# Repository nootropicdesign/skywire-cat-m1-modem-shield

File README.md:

# Skywire Shield: Arduino shield for Nimbelink Skywire CAT M1 and NB-IoT modems

This is a design for a simple Arduino shield for Nimbelink Skywire CAT M1 and NB-IoT modems. Nimbelink modems are designed to have compatible pinouts and electrical characteristics, so it is possible to design a carrier board that works for a large variety of modems. The board has a switching power supply that provides 3.8V to the modem. Jumpers can be used to connect the modem's serial RX and TX to the Arduino hardware serial pins or to pins for use with software serial (digital pins 2 and 3).

A standard 6-pin serial header connection is accessible from the bottom of the board. This is because some modem modules come with a very high default serial rate that must be changed before an Arduino can interface with it. For example, the Sequans Monarch modem has a default rate of 921600. Connect with a terminal program on a computer and change this with the command `AT+IPR=19200`.

For a full description of this project, see [this project on the nootropic design Project Lab site](https://nootropicdesign.com/projectlab/2019/04/21/arduino-shield-for-cat-m1-and-nb-iot-modems/).

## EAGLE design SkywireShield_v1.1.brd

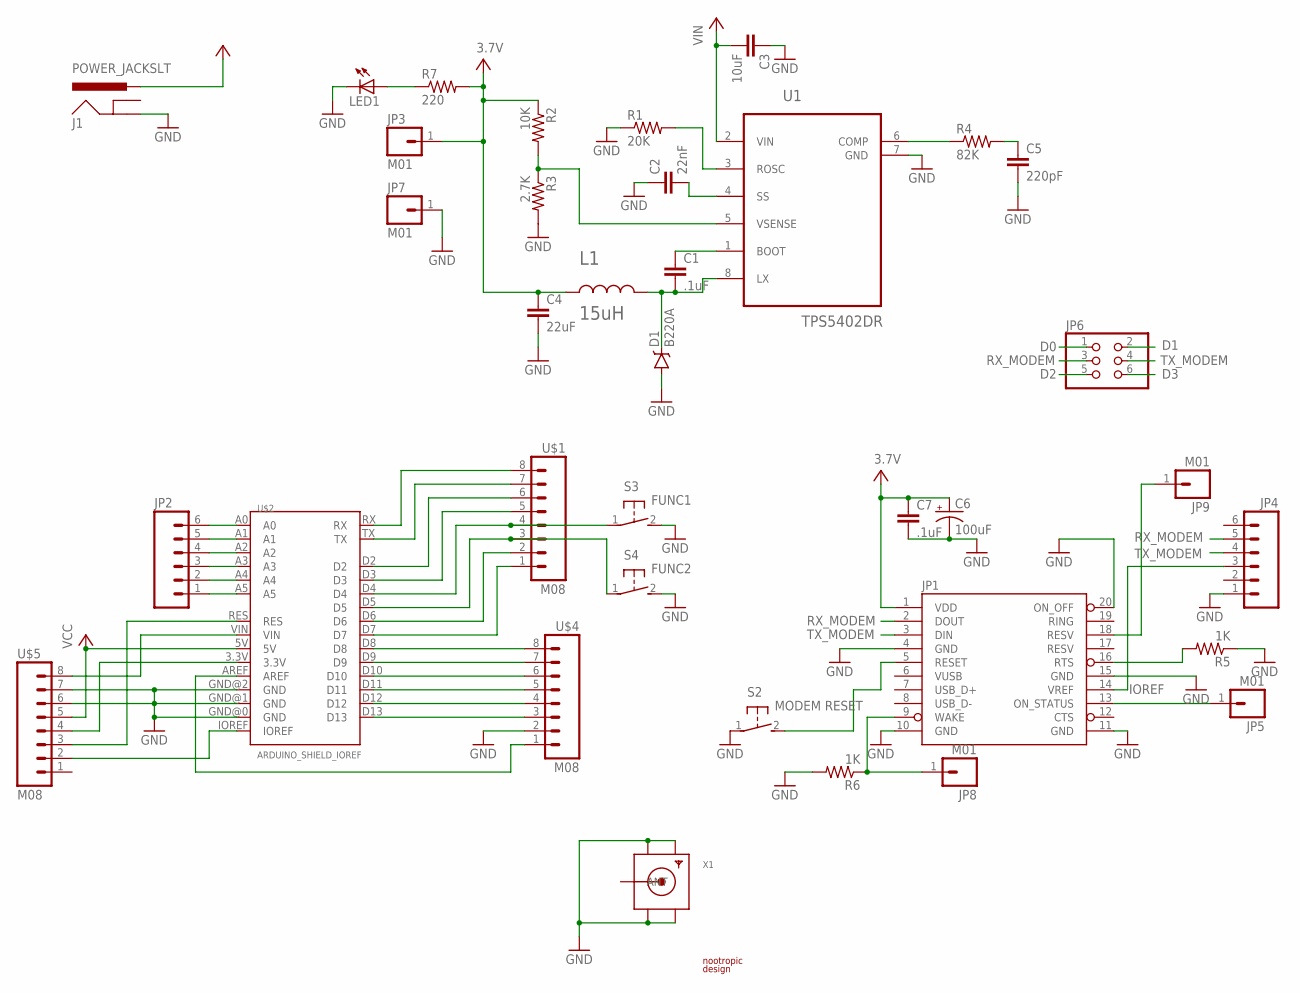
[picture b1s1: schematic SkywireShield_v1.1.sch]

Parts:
C1, C7: .1uF; C0603
C2: 22nF; C0603
C3: 10uF; C0603
C4: 22uF; C0603
C5: 220pF; C0603
C6: 100uF; PANASONIC_D
D1: B220A; SMA-DIODE
J1: POWER_JACKSLT; POWER_JACK_SLOT
JP1: SKYWIRE_MODEM; SKYWIRE-SOCKET
JP2, JP4: M06; 1X06
JP3, JP5, JP7, JP8, JP9: M01; 1X01
JP6: PINHD-2X3SERIAL-SELECTOR; 2X03-SERIAL-SELECTOR
L1: 15uH; IND_VLS5045EX
LED1: LEDCHIPLED_0805; CHIPLED_0805
R1: 20K; R0603
R2: 10K; R0603
R3: 2.7K; R0603
R4: 82K; R0603
R5, R6: 1K; R0603
R7: 220; R0603
S2: MODEM RESET; DTSM-3
S3: FUNC1; DTSM-3
S4: FUNC2; DTSM-3
U1: TPS5402DR; SOIC8
U$1, U$4, U$5: M08; 1X08
U$2: ARDUINO_SHIELD_IOREF; ARDUINO_SHIELD_GENERIC
U$3: LOGO; LOGO_SMALL
X1: SMACONNECTOR; SMA90_DIP

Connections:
D0: JP6.1, U$1.8, U$2.RX
D1: JP6.2, U$1.7, U$2.TX
D2: JP6.5, U$1.6, U$2.D2
D3: JP6.6, U$1.5, U$2.D3
D4: S3.1, U$1.4, U$2.D4
D5: S4.1, U$1.3, U$2.D5
D6: U$1.2, U$2.D6
D7: U$1.1, U$2.D7
D8: U$2.D8, U$4.8
FB: R2.2, R3.1, U1.5 (VSENSE)
GND: C2.1, C3.1, C4.2, C5.2, C6.-, C7.2, D1.A, J1.GND, JP1.4 (GND), JP1.10 (GND), JP1.11 (GND), JP1.15 (GND), JP1.20 (ON_OFF), JP4.1, JP7.1, LED1.C, R1.1, R3.2, R5.1, R6.2, S2.1, S3.2, S4.2, U1.7 (GND), U$2.GND@0 (GND), U$2.GND@1 (GND), U$2.GND@2 (GND), U$4.2, U$5.6, U$5.7, X1.GND1, X1.GND2, X1.GND3, X1.GND4
IOREF: JP1.14 (VREF), JP4.3, U$2.IOREF, U$5.2
unnamed: JP1.18 (RESV), JP9.1
unnamed: LED1.A, R7.1
unnamed: JP1.16 (RTS), R5.2
unnamed: R1.2, U1.3 (ROSC)
unnamed: C1.1, U1.1 (BOOT)
unnamed: C1.2, D1.C, L1.2, U1.8 (LX)
unnamed: U$2.3.3V, U$5.4
unnamed: JP1.5 (RESET), S2.2
unnamed: U$2.D9, U$4.7
unnamed: U$2.D10, U$4.6
unnamed: U$2.D11, U$4.5
unnamed: U$2.D12, U$4.4
unnamed: U$2.D13, U$4.3
unnamed: C2.2, U1.4 (SS)
unnamed: U$2.AREF, U$4.1
unnamed: JP2.6, U$2.A0
unnamed: JP2.5, U$2.A1
unnamed: JP2.4, U$2.A2
unnamed: JP2.3, U$2.A3
unnamed: JP2.2, U$2.A4
unnamed: JP2.1, U$2.A5
unnamed: U$2.VIN, U$5.8
unnamed: R4.1, U1.6 (COMP)
unnamed: C5.1, R4.2
ON_STATUS: JP1.13 (ON_STATUS), JP5.1
RESET: U$2.RES, U$5.3
RX_MODEM: JP1.2 (DOUT), JP4.5, JP6.3
TX_MODEM: JP1.3 (DIN), JP4.4, JP6.4
V+: C4.1, C6.+, C7.1, JP1.1 (VDD), JP3.1, L1.1, R2.1, R7.2
VCC: U$2.5V, U$5.5
VIN: C3.2, J1.PWR, U1.2 (VIN)
VUSB: JP1.6 (VUSB)
WAKE: JP1.9 (WAKE), JP8.1, R6.1

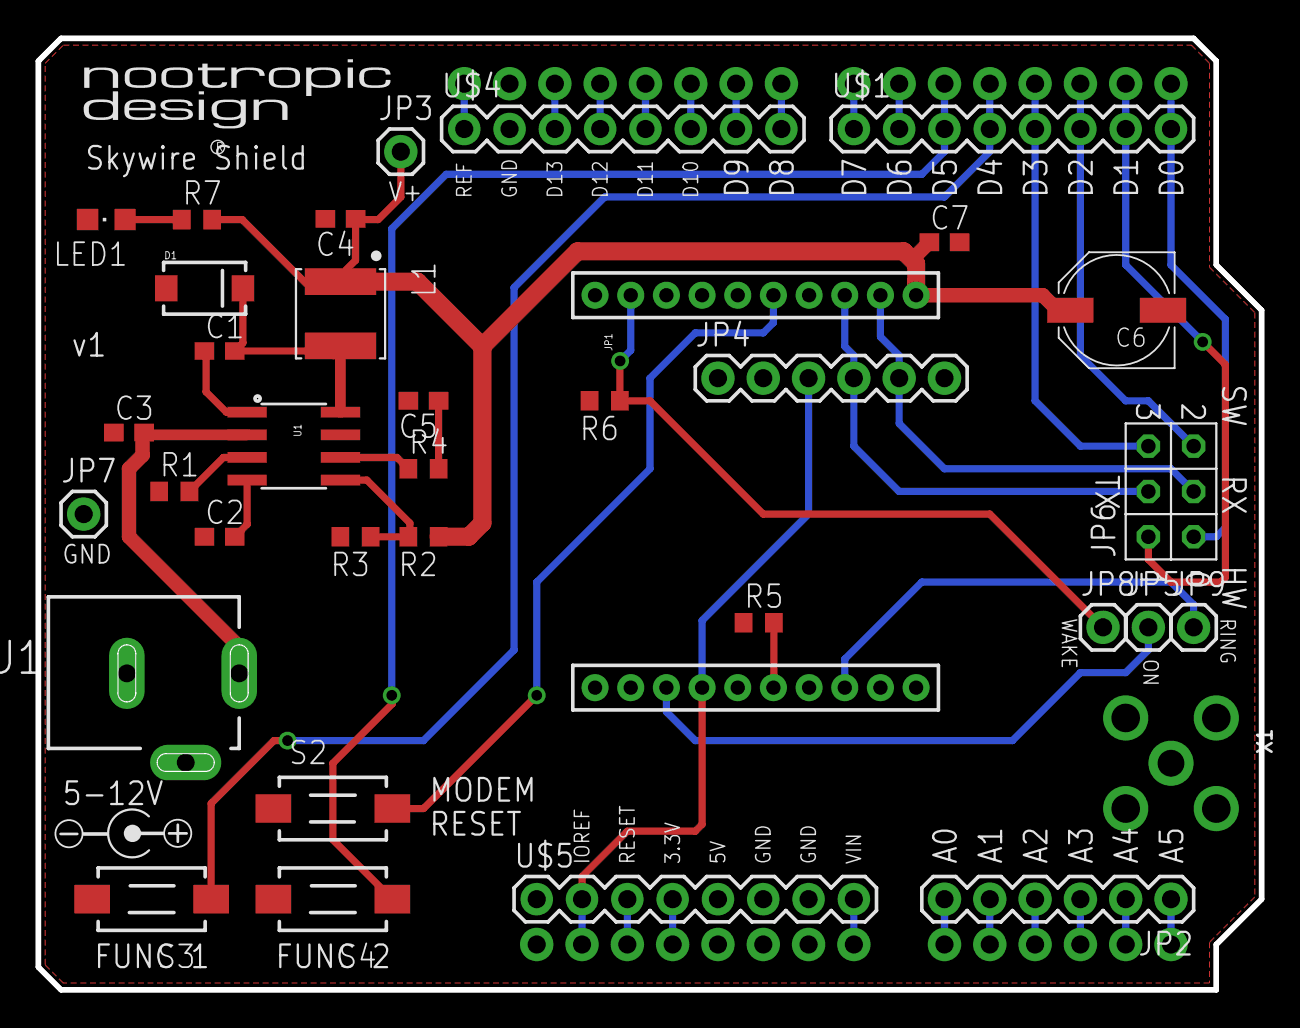
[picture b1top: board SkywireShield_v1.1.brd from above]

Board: 2 copper layers, 68.6 x 53.3 mm, 37 parts (0 on the bottom side), 44 nets.

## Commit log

2019-04-20 Initial revision.
2019-04-21 Updated README.

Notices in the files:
parts and their libraries:
microbuilder: This work is placed in the public domain, and may be freely used for commercial and non-commercial work with the following conditions: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
SparkFun-DiscreteSemi: Licensing: Creative Commons ShareAlike 4.0 International - https://creativecommons.org/licenses/by-sa/4.0
